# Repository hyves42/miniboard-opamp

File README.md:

miniboard-opamp
===============

This is a prototyping board for most surface-mount op-amp.
It has a surface-mount prototyping to build all common op-amp filter topologies.

Here is what it looks like :

Front

Features :
* A footpint for an SO-8 op-amp
* Local power regulation
* SMD prototyping pads.

The board is made with Kicad and requires a 2015 version for editing (with .pretty footprint libraries support)

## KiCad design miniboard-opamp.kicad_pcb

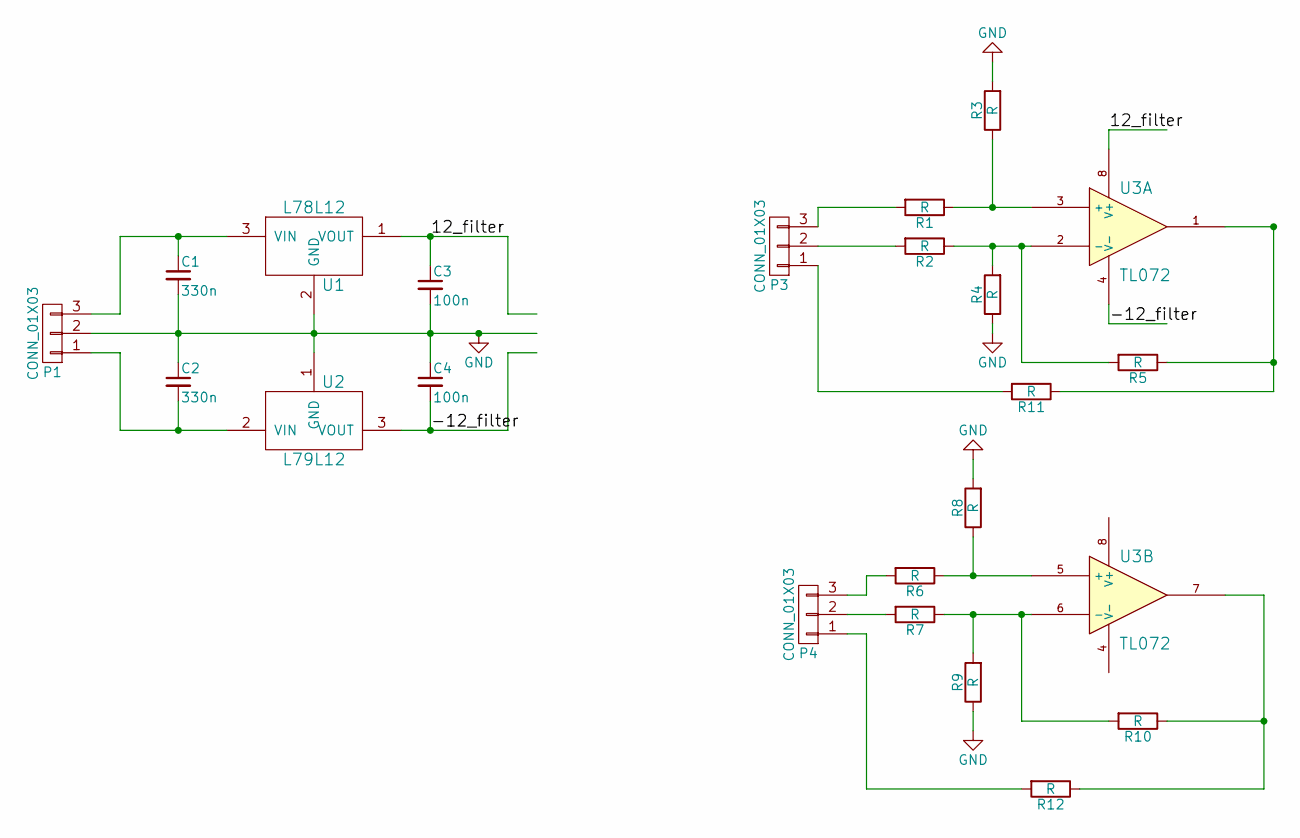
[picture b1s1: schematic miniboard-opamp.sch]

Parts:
C1, C2: 330n; C_0603_HandSoldering
C3, C4: 100n; C_0603_HandSoldering
P1, P3, P4: CONN_01X03; Socket_Strip_Straight_1x03
R1, R2, R3, R4, R5, R6, R7, R8, R9, R10, R11, R12: R; R_0603_HandSoldering
U1: L78L12; SOT89-3_Housing
U2: L79L12; SOT89-3_Housing
U3: TL072; SOIC-8_3.9x4.9mm_Pitch1.27mm

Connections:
/12_filter: C3.1, U1.1 (VOUT), U3.8 (V+)
/-12_filter: C4.2, U2.3 (VOUT), U3.4 (V-)
GND: C1.2, C2.1, C3.2, C4.1, P1.2, R3.2, R4.1, R8.2, R9.1, U1.2 (GND), U2.1 (GND)
unnamed: C1.1, P1.3, U1.3 (VIN)
unnamed: C2.2, P1.1, U2.2 (VIN)
unnamed: P3.1, R11.2
unnamed: P3.2, R2.2
unnamed: P3.3, R1.2
unnamed: P4.1, R12.2
unnamed: P4.2, R7.2
unnamed: P4.3, R6.2
unnamed: R1.1, R3.1, U3.3 (+)
unnamed: R2.1, R4.2, R5.2, U3.2 (-)
unnamed: R6.1, R8.1, U3.5 (+)
unnamed: R10.1, R12.1, U3.7
unnamed: R7.1, R9.2, R10.2, U3.6 (-)
unnamed: R5.1, R11.1, U3.1

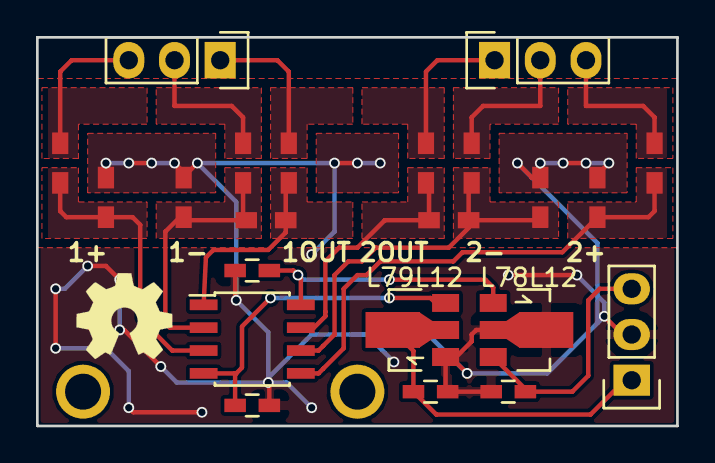
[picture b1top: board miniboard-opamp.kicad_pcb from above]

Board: 2 copper layers, 35.6 x 21.6 mm, 25 parts (0 on the bottom side), 17 nets.

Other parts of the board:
hole_2mm, hole_2mm#2, hole_2mm#3: VAL**; hole_2mm

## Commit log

2015-10-24 Start routing
2015-10-26 1st version finished
2016-02-24 Re generate gerbers, export to pdf
2016-03-10 Move dimension to dwg layer
